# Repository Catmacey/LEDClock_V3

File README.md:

Circular LED Clock
==================

This is an digital LED "Analogue" clock using 60 dicrete LEDs in a circular pattern.
It's an old project built on two single sided boards. The boards are designed for easy home fabrication using the toner transfer technique.  The CPU board uses all DIP parts, the display board uses surface mount LEDs in 1206 package.

The MCU is a 18f2525 with a Maxim MAX6956 driving the LEDs and a Maxim DS1307 keeping time.

[More information is available on my blog.](http://catmacey.wordpress.com/projects/led-clock-project/led-clock-project-details/)

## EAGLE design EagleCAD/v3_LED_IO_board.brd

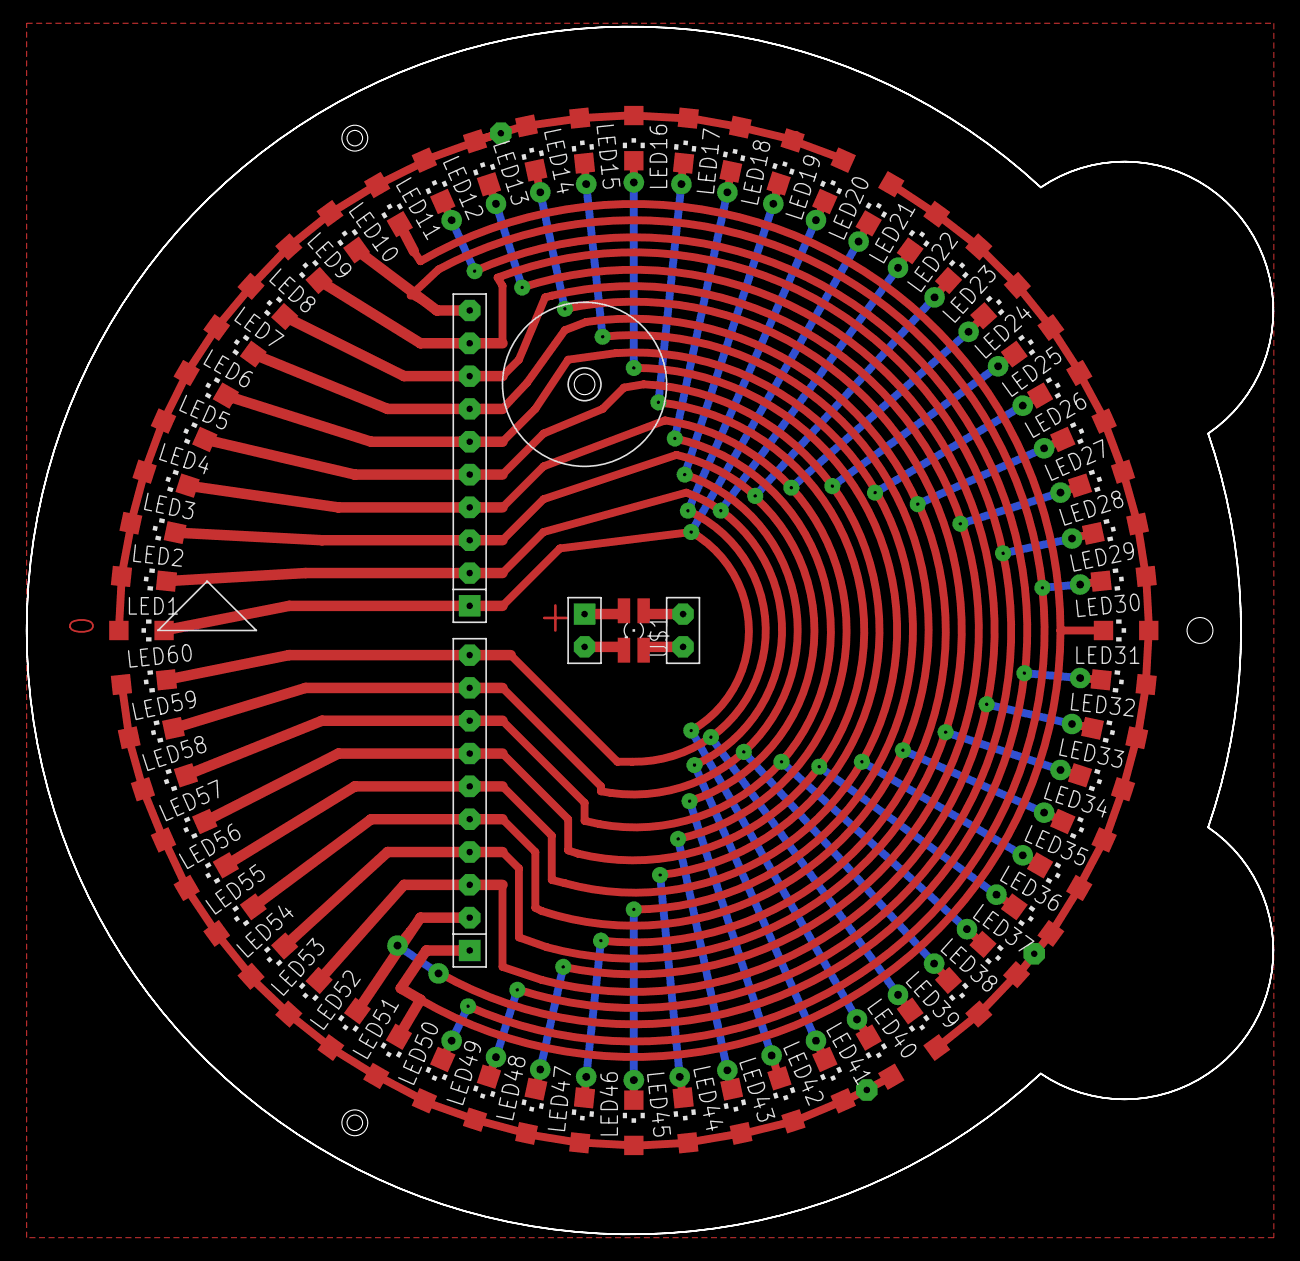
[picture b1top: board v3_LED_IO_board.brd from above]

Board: 2 copper layers, 96.5 x 93.5 mm, 62 parts (0 on the bottom side), 27 nets.

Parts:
LED1, LED2, LED3, LED4, LED5, LED6, LED7, LED8, LED9, LED10, LED11, LED12, LED13, LED14, LED15, LED16, LED17, LED18, LED19, LED20, LED21, LED22, LED23, LED24, LED25, LED26, LED27, LED28, LED29, LED30, LED31, LED32, LED33, LED34, LED35, LED36, LED37, LED38, LED39, LED40, LED41, LED42, LED43, LED44, LED45, LED46, LED47, LED48, LED49, LED50, LED51, LED52, LED53, LED54, LED55, LED56, LED57, LED58, LED59, LED60: CHIPLED_1206
U$1: RGBLED; 1206_RGBLED
U$2: LEDCLOCK_FRONT

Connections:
+5V: U$1.A, U$2.+5V
LED6: LED6.C, LED26.C, LED46.C, U$2.JL6
unnamed: LED9.C, LED29.C, LED49.C, U$2.JL9
unnamed: LED1.A, LED2.A, LED3.A, LED4.A, LED5.A, LED6.A, LED7.A, LED8.A, LED9.A, LED10.A, LED11.A, LED12.A, LED13.A, LED14.A, LED15.A, LED16.A, LED17.A, LED18.A, LED19.A, LED20.A, U$2.BANK1
unnamed: LED1.C, LED21.C, LED41.C, U$2.JL1
unnamed: LED2.C, LED22.C, LED42.C, U$2.JL2
unnamed: LED3.C, LED23.C, LED43.C, U$2.JL3
unnamed: LED4.C, LED24.C, LED44.C, U$2.JL4
unnamed: LED5.C, LED25.C, LED45.C, U$2.JL5
unnamed: U$1.R, U$2.JIN1
unnamed: LED7.C, LED27.C, LED47.C, U$2.JL7
unnamed: LED19.C, LED39.C, LED59.C, U$2.JL19
unnamed: LED10.C, LED30.C, LED50.C, U$2.JL10
unnamed: U$1.B, U$2.JIN2
unnamed: U$1.G, U$2.JIN3
unnamed: LED8.C, LED28.C, LED48.C, U$2.JL8
unnamed: LED21.A, LED22.A, LED23.A, LED24.A, LED25.A, LED26.A, LED27.A, LED28.A, LED29.A, LED30.A, LED31.A, LED32.A, LED33.A, LED34.A, LED35.A, LED36.A, LED37.A, LED38.A, LED39.A, LED40.A, U$2.BANK2
unnamed: LED11.C, LED31.C, LED51.C, U$2.JL11
unnamed: LED12.C, LED32.C, LED52.C, U$2.JL12
unnamed: LED13.C, LED33.C, LED53.C, U$2.JL13
unnamed: LED14.C, LED34.C, LED54.C, U$2.JL14
unnamed: LED15.C, LED35.C, LED55.C, U$2.JL15
unnamed: LED17.C, LED37.C, LED57.C, U$2.JL17
unnamed: LED18.C, LED38.C, LED58.C, U$2.JL18
unnamed: LED20.C, LED40.C, LED60.C, U$2.JL20
unnamed: LED41.A, LED42.A, LED43.A, LED44.A, LED45.A, LED46.A, LED47.A, LED48.A, LED49.A, LED50.A, LED51.A, LED52.A, LED53.A, LED54.A, LED55.A, LED56.A, LED57.A, LED58.A, LED59.A, LED60.A, U$2.BANK3
unnamed: LED16.C, LED36.C, LED56.C, U$2.JL16

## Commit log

2014-08-27 Initial loading of archived files
2014-08-27 Create LICENSE
2014-08-29 Project source and compiled HEX
